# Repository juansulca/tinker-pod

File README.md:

# TinkerPod

Open-Source | DIY | Multitool | Modular | Extendable

The TinkerPod is an Open-Source hardware platform designed to appeal to makers, creative coders,
and designers by providing a hackable and customizable hardware. Inspired by the evolution of
multitools and influenced by contemporary devices like the Flipper Zero and SQRT,
this project explores the application of critical making, and personal fabrication to Open-Source hardware.
The TinkerPod is an ideal hardware platform for designers and makers to explore, learn, modify and extend; make it your own!

## Versions

The TinkerPod was designed to have 3 versions. All the versions are currently supported.
The main difference between versions is the parts list, complexity of assembly and features.

- [v1 TinkerArt](v1/): This version offers generative art functionality and can be programmed to create unique art pieces.
- [v2 TinkerPlay](v2/): This version offers a variety of games and functions, including games like pong, a timer, an etch-a-sketch inspired drawing function
  and a generative art function out of the box.
- [v3 TinkerPod](v3/): This version is an enhanced version of v2, running the same firmware but with additional features like a vibratioin sensor,
  hardware debouncing for the buttons and a fully integrated PCB.

## Hardware

This project was designed to work around the QT PY RP2040 from Adafruit. Despite this, it is possible to run the TinkerPod with
other microcontrollers with the same pinout and form factor from other manufacturers. This includes other boards from
Adafruit (QT PY line), the XIAO boards from Seeed Studio, among others.

TinkerPod v1, does not include a PCB and can be wired without tools using a tiny solderless breadboard, the display, microcontroller, and the case.

For ease of assembly starting from V2, the Screen for the TinkerPod is a 1.5" grayscale OLED display with the SSD1327 controller using a STEMMA cable. This display can be found from Adafruit and
other manufacturers but the Adafruit version is recommended due to the STEMMA cable, that reduces complexity for the assembly.

The TinkerPod v2 and v3 include PCB designs and schematics and require soldering.
A detailed assembly guide can be found along side the version files.

The hardware for this project took inspiration from the following sources:

- [Adafruit Charger BFF for QT Py](https://github.com/adafruit/Adafruit-Charger-BFF-PCB?tab=readme-ov-file#adafruit-charger-bff-for-qt-py-pcb)
- [Soldered Inkplate 2](https://github.com/SolderedElectronics/Soldered-Inkplate-2-hardware-design/tree/main)

## Firmware

All versions of the TinkerPod run on CircuitPython. The included firmware includes assets and base functionality.
You can modify the the firmware and add or change the functionality of the TinkerPod.

If you want to get started writing your own firmware and functionality, you can start with the [examples](examples/) directory.
This will provide the bassis for modifying the firmware and adding new functionality.

## Case

The case for the TinkerPod designed for 3D printing and can be printed using any FDM printer.
Printing settings are provided with each version files.

The cases for all versions were tested and printed using PLA and PETG. With the best results being
achieved with PETG on a textured plate.

Alternative cases can be found in the variants directory.

## Documentation

General guides can be found in the [docs](docs/) directory, including a simple guide to install CircuitPython and
managing the dependencies for the firmware.

## Acknowledgements

The hardware for this project took inspiration from the following sources:

- [Adafruit Charger BFF for QT Py](https://github.com/adafruit/Adafruit-Charger-BFF-PCB)
- [Soldered Inkplate 2](https://github.com/SolderedElectronics/Soldered-Inkplate-2-hardware-design/tree/main)
- [SQRT](https://ksawerykomputery.com/works/sqrt)
- [Button debounce article](https://hackaday.com/2015/12/09/embed-with-elliot-debounce-your-noisy-buttons-part-i/)

## Contributions

Contributions are welcome and appreciated. If you have any suggestions or improvements, please feel free to open an issue or submit a pull request.

## License

The TinkerPod is licensed under the following terms:

- Software: MIT License (see [LICENSE](LICENSE))
- Hardware: CERN Open Hardware Licence Version 2 - Permissive (see [LICENSE_OHL](LICENSE_OHL))
- Documentation: CC-BY-SA-4.0 (see [LICENSE_CC](LICENSE_CC))

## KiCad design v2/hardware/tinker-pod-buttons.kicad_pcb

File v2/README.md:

# TinkerPod v2

TinkerPod v2 is a more advanced version of the tinkerpod. This version includes 4 buttons and an optional LiIon charger and battery.
This version can be powered using a USB-C cable with a powerbank, phone or USB-C charger.
The firmware included with this version includes more applications and a application menu.

## Parts List

| Item                              | Quantity | Description                                          |
| --------------------------------- | -------- | ---------------------------------------------------- |
| Adafruit QT PY RP2040             | 1        | Can be replaced with XIAO pinout boards              |
| Adafruit 1.5" Gray scale OLED     | 1        | SSD1327 driver chip, SPI/I2C interface               |
| TinkerPod v2 PCB                  | 1        |                                                      |
| STEMMA QT/Qwiic cable             | 1        | 50mm long                                            |
| Push buttons                      | 4        | 8mm rubber dome push buttons                         |
| Adafruit LiIon Charger BFF Add-On | 1        | (Optional battery powered)                           |
| Lithium Ion Polymer Battery       | 1        | (Optional battery powered) 3.7v – 420mAh single cell |
| Threaded Inserts                  | 8        |                                                      |
| M2 machine screws                 | 8        | M2 size bolts (4mm x2, 6mm x6)                       |
| TinkerPod v2 3D printed case      | 1        |                                                      |

## Required tools:

| Item           | Description                             |
| -------------- | --------------------------------------- |
| Soldering Iron | Preferably one with a fine tip          |
| Solder         | Rosin core, preferably thin             |
| Flux           | Paste or pen                            |
| Hex key        | Or screw driver depending on the screws |
| Twezzers       | (optional)                              |
| USB-C cable    | USB C **data** cable (USB C to C/A)     |

## Assembly

1. Flash circuit python on the QT PY RP2040.
   1. Open the official [site](https://circuitpython.org/board/adafruit_qtpy_rp2040/) and download the latest version of CircuitPython.
   2. While holding the _boot_ button in the QT PY, plug it into a computer using the USB-C cable. Different version of the QT PY might need a different button to access bootloader mode, please check the official [docs](https://learn.adafruit.com/welcome-to-circuitpython/installing-circuitpython) for the specific board.
      
   3. The device should appears mounted in the OS as **RPI-RP2**, this might be different for other boards other than the RP2040 board.
   4. Drag and drop the `.UF2` file (downloaded in step 1) to the `RPI-RP2` boot drive.
   5. After a couple of seconds the onboard neopixel (LED) will flash and a new drive will appear in the computer, this time it should be called **CIRCUITPY**.
   6. ⚠️ Always eject the device before unplugging the cable.
2. (Optional) Solder the LiIon Charger BFF to the PCB.
   1. Place the PCB donut side down. The **TinkerPod** and **v2** silkscreen labels should be visible.
   2. Carefully line up the BFF with the PCB, in the M2 space, also marked as BFF LiPo charger. The JST connector (white box) should be facing the **v2** text on the PCB.
      
   3. Solder all the pads. take extra care on the 5V and GND pads.
      
3. Solder the QT PY to the PCB.
   1. Place the PCB donut side down. The **TinkerPod** and **v2** silkscreen labels should be visible.
   2. Carefully line up the QT PY with the PCB, in the `M1` space also marked on the side as `QT PY RP2040`. The pads can be identified for the cutout in the middle. Make sure the USB port is pointing towards the outside of the board and the reset and boot buttons and the STEMMA connector are accessible.
      
   3. Solder the **14** pins, 7 on each side.
      
4. Solder the 4 buttons to the PCB.
   1. After completing steps 2 and 3, flip the PCB (Donut side up).
      
   2. Place the buttons in the markers SW1, SW2, SW3, SW4.
      
   3. Flip the PCB again (Donut side down).
   4. Solder all 4 pins of every push button. (16 solder joins in total).
      
5. Now is a great moment to flash the firmware and test the TinkerPod before installing it into the case.
   1. Connect the STEMMA connector to the QT PY and Screen. It should slide in place without force.
      
   2. (Optional) Connect the battery using the JST connector in the BFF board.
      
   3. Download the TinkerPod firmware from GitHub. (firmware folder)
   4. Using a USB C data cable. Plug the device to the computer.
   5. Copy the content of the firmware folder (where the `code.py`file is) to the device.
   6. Remember to copy the `lib`directory.
   7. Alternatively check this project documentation for alternative installation methods.
   8. The splash screen followed by the menu should appear. Navigate the menu and use the applications by pressing the 4 buttons.
   9. The charging indicator (orange LED) in the BFF board should light up if there is a battery connected and the BFF installed.
      
   10. If everything works as expected, continue with the next step.
       1. If something is not working:
       2. Check for cold solder joins
       3. Verify that that the firmware was flashed correctly.
       4. If there is red LED flashing there is an issue with the firmware.
   11. Eject the device and unplug the USB cable.
6. Place the 3D printed buttons in the enclosure and make sure they slide smooth.
   
7. Prepare the bottom enclosure.
   1. Place the threaded inserts in the holes located in the top part of the enclosure.
      
   2. Using the soldering iron push the inserts as straight as possible until they are flush with the surface of the enclosure.
      
   3. Place the PCB in place (with the USB-C port towards the hole in the enclosure) and screw it in place using the M2 machine screws.
   4. Make sure the power switch on the BFF board is in the _off_ position.
   5. Plug in the battery.
      
   6. Secure the battery using the battery bracket and some double sided tape.
8. Prepare the screen assembly
   1. Place the threaded inserts in the holes located in the top part of the enclosure.
   2. Using the soldering iron push the inserts as straight as possible until they are flush with the surface of the case.
      
   3. Connect the STEMMA cable into the screen, it should slide in place without force.
   4. Gently place the 1.5" screen into the slot, do not apply pressure on the scree.
      
   5. Place the screen supports and line up the holes. The rectangular piece should go towards the top (can be placed in any orientation) and the remaining piece should go to the bottom. The bottom piece will only line up one way, with the legs pointing to the top.
   6. Screw the supports to the top case, tighten the screws until there is some resistance. Do not over tighten the screws.
      
   7. The screen might have some play, this is expected. And some gaps might be visible from the front side, which is also expected.
9. Closing the case.
   1. Plug the other side of the STEMMA connector to the QT PY.
      
   2. Using the power switch in the BFF board, turn the device _on_.
   3. Gently push the two parts of the case together.
10. Happy tinkering!

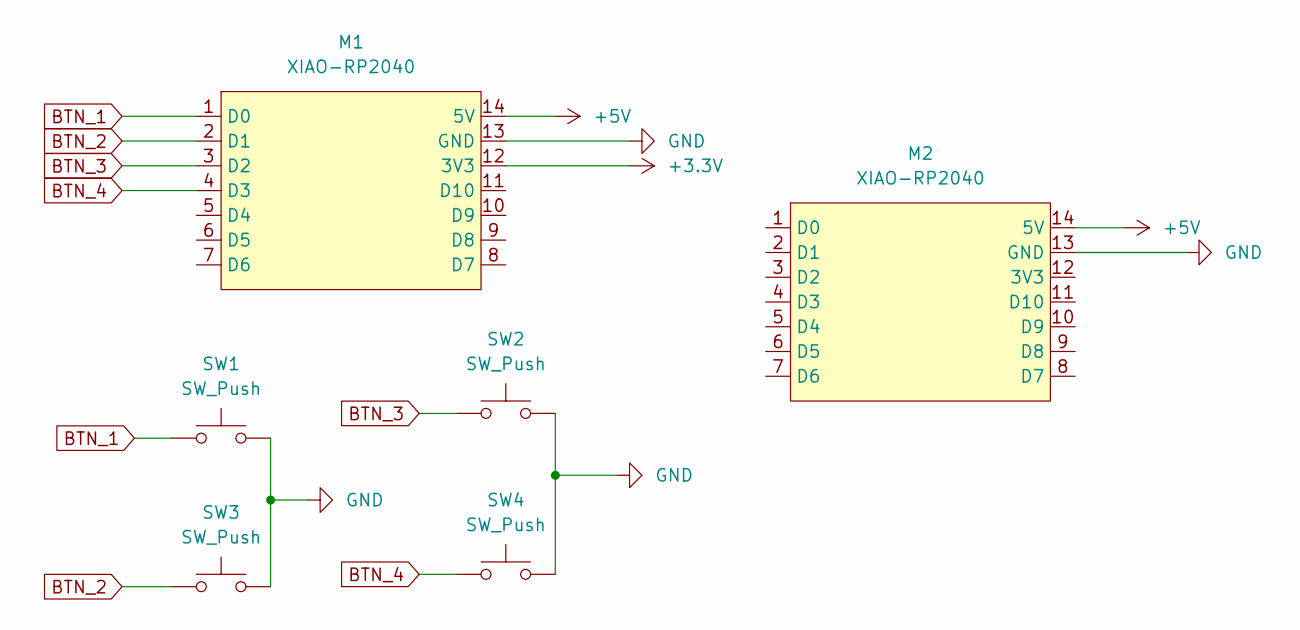
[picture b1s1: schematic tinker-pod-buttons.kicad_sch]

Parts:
M1: XIAO-RP2040; QTPYRP2040
M2: XIAO-RP2040; XIAO-SAMD21-RP2040-14P-2.54-21X17.8MM (Seeeduino XIAO)
SW1, SW2, SW3, SW4: SW_Push; 3101

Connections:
+3.3V: M1.12 (3V3)
+5V: M1.14 (5V), M2.14 (5V)
BTN_1: M1.1 (D0), SW1.1
BTN_2: M1.2 (D1), SW3.1
BTN_3: M1.3 (D2), SW2.1
BTN_4: M1.4 (D3), SW4.1
GND: M1.13 (GND), M2.13 (3V3), SW1.2, SW2.2, SW3.2, SW4.2

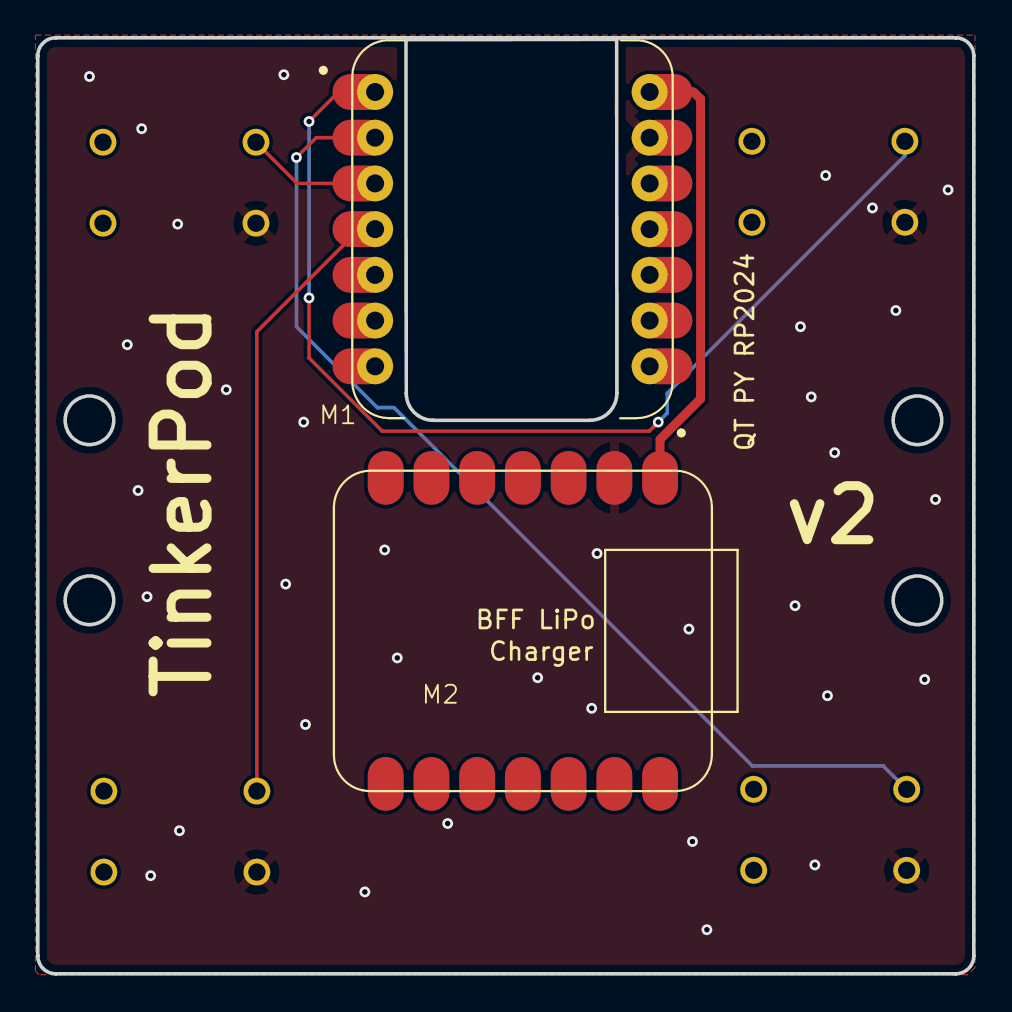
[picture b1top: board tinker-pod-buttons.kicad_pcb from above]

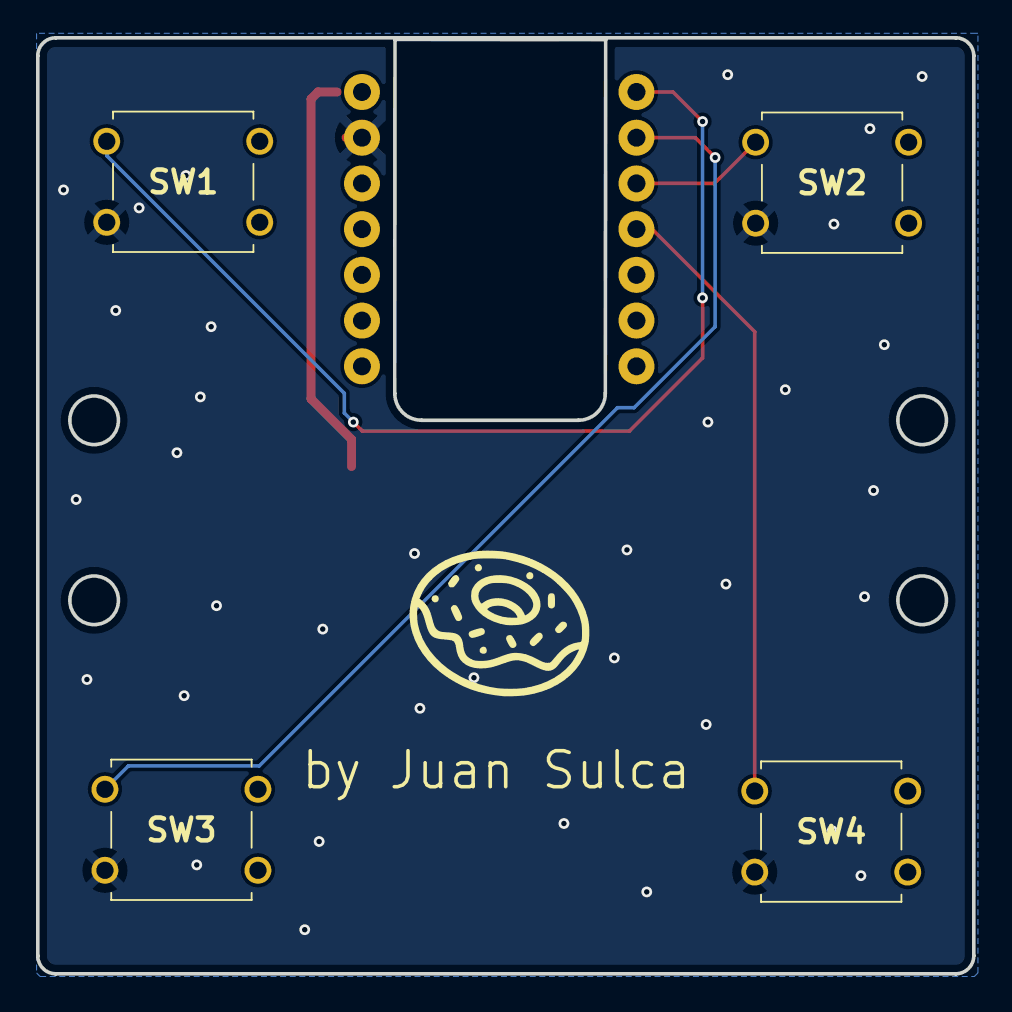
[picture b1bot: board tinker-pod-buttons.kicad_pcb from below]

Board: 2 copper layers, 52.0 x 52.0 mm, 6 parts (4 on the bottom side), 6 nets.

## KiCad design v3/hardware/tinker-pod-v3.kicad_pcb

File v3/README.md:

# TinkerPod v3 (latest)

The latest evolution of TinkerPod delivers enhanced functionality and streamlined design through single-PCB integration. This version builds upon its predecessors, offering improved features and more robust implementation while maintaining the platform's core functionality.

The CAD and productions files for v3 con be found in the [hardware](hardware/) directory. Which is devided in:

- PCB
  - Schematic
  - PCB Layout
  - Bill of Materials
  - Gerber Files
- Case
  - Case Design
  - 3D models

The assembly instruction can be found on this page.

## v3 PCB

### Bill Of Materials

| Qty | Value                        | Package        | Designator     | Part number                              |
| :-- | ---------------------------- | -------------- | -------------- | ---------------------------------------- |
| 4   | .1uF, ceramic, 25V, 10%, X5R | 1210           | C1, C2, C3, C4 | KEMET - C1210X104K1RACTU                 |
| 2   | 10uF, ceramic, 16V, 10%, X5R | 1210           | C5, C6         | KEMET - C1210C106K3RACAUTO               |
| 1   | LED                          | 1206           | D1             | Broadcom - HSMG-C150                     |
| 1   | Schottky Diodes, 1A, 20V     | SOD-123        | D2             | onsemi - MBR120ESFT1G                    |
| 1   | B2B-PH-SM4-TB                | B2BPHSM4TBLFSN | J1             | JST - B2BPHSM4TBLFSN                     |
| 4   | 1K, 1/4W, 1%                 | 1206           | R1, R2, R3, R4 | Vishay / Beyschlag - MCA12060C1001FP500  |
| 2   | 5.1K, 1/4W, 0.1%             | 1206           | R5, R6         | Panasonic - ERA-8ARB512V                 |
| 1   | MCP73831T-2ACI/OT            | SOT-23-5       | U2             | Microchip Technology - MCP73831T-2ACI/OT |
| 1   | DPDT                         | JS202011AQN    | S5             | C&K - JS202011AQN                        |

### Assembly

1. Secure the PCB with the TP v3 label facing up.
   
2. Apply paste in all the SMD pads, except for the QT PY pads, D1 and J1.
   1. Best results were achieved soldering the LED (D1) and JST (J1) connector with a soldering iron.
   2. Apply solder paste to the pads, but enough to cover the pad but not a blob bigger than the pad.
      
3. Use tweezers or a tiny plastic point to remove excess solder paster.
4. Place the components that do not have polarity.
   1. Place C1, C2, C3, C4 - the .1uF capacitors.
   2. Place R1, R2, R3, R4 - 1k resistors.
   3. Place C5, C6 - 10uF capacitors.
      
   4. Place R5, R6 - 5.1K resistors.
5. Place the components with polarity

   1. Place D2: diode with the line facing the closed side of the rectangle
   2. Place U2: the battery charging IC

      1. The side with 3 legs should match the side with the tiny arrow

6. Solder the components using a hot air reflow station.
   1. According to the specification of the solder paste, set the temperature, starts from the lowest recommended temperature.
   2. Start from far away with a medium to low airflow.
   3. Approach the individual components and make sure they fall correctly into place.
      
   4. After all components are soldered, visually inspect the joints, make sure the are no pads shorting and that all the paste melted. Be careful, the PCB might be hot
      
   5. If there are shorting pads, retouch them with a soldering iron and some flux.
7. Solder D1 LED
   1. Check the polarity of the LED
   2. Place the LED with the Cathode (-) towards the closed side of the rectangle
   3. With the help of tweezers , solder the LED in place with a soldering iron.
      
8. Solder J1 JST connector.
   1. Apply some flux on the pads.
   2. Place the JST connector in place, aligning the box with the body of the connector.
   3. With the soldering iron carefully solder one of the legs of the connector.
   4. Solder the remaining legs, not much solder is needed.
      
9. Solder the S5 slide switch.
   1. Place the switch from the side. (TP v3 side)
      
   2. Flip The PCB (Tinkerpod pixelated logo up)
   3. Solder the six pins.
      
10. The PCB assembly will continue in the next section.

## Parts List

| Item                          | Quantity | Description                             |
| ----------------------------- | -------- | --------------------------------------- |
| Adafruit QT PY RP2040         | 1        | Can be replaced with XIAO pinout boards |
| Adafruit 1.5" Gray scale OLED | 1        | SSD1327 driver chip, SPI/I2C interface  |
| TinkerPod v3 PCB              | 1        |                                         |
| STEMMA QT/Qwiic cable         | 1        | 50mm long                               |
| Push buttons                  | 4        | 8mm rubber dome push buttons            |
| Threaded Inserts              | 8        |                                         |
| M2 machine screws             | 8        | M2 size bolts (4mm x2, 6mm x6)          |
| TinkerPod v2 3D printed case  | 1        |                                         |

## Assembly

1. Flash circuit python on the QT PY RP2040.
   1. Open the official [site](https://circuitpython.org/board/adafruit_qtpy_rp2040/) and download the latest version of circuit python.
   2. While holding the _boot_ button in the QT PY, plug it into a computer using the USB-C cable. Different version of the QT PY might need a different button to access bootloader mode, please check the official [docs](https://learn.adafruit.com/welcome-to-circuitpython/installing-circuitpython) for the specific board.
      
   3. The device should appears mounted in the OS as **RPI-RP2**, this might be different for other boards other than the RP2040 board.
   4. Drag and drop the `.UF2` file (downloaded in step 1) to the `RPI-RP2` boot drive.
   5. After a couple of seconds the onboard neopixel (LED) will flash and a new drive will appear in the computer, this time it should be called **CIRCUITPY**.
   6. ⚠️ Always eject the device before unplugging the cable.
2. Solder the QT PY to the PCB.
   1. Place the PCB with the pixelated Tinkerpod logo facing down. The **TP v3** should be visible.
      
   2. Carefully line up the QT PY with the PCB, in the `QT PY RP2040` space. The pads can be identified for the cutout in the middle. Make sure the USB port is pointing towards the outside of the board and the reset and boot buttons and the STEMMA connector are accessible.
   3. Solder the **14** pins, 7 on each side.
      
3. Solder the 4 buttons to the PCB.
   1. Flip the PCB (pixelated TinkerPod logo facing up).
   2. Place the buttons in the markers SW1, SW2, SW3, SW4.
      
   3. Flip the PCB again (pixelated Tinkerpod logo facing down).
   4. Solder all 4 pins of every push button. (16 solder joins in total).
      
4. Solder the vibration sensor
   1. Bend the vibration sensor legs to 90 degrees.
   2. Put the vibration sensor into the SW1 slot. The vibration sensor does not have polarity.
      
   3. If needed use some tape to secure the vibration sensor in place while soldering.
   4. Flip the PCB (Tinkerpod logo up)
   5. Solder the two pins.
      
   6. If the pins seem a bit long, cut them with a pair of flush cutters.
      
5. Now is a great moment to flash firmware and test the TinkerPod before installing it into the case.
   1. Connect the STEMMA connector to the QT PY and Screen. It should slide in place without force.
   2. (Optional) Connect the battery using the JST connector in the BFF board.
   3. Download any of the TinkerPod examples from GitHub. (examples folder)
   4. Using a USB C data cable. Plug the device to the computer.
   5. Copy the content of the firmware folder (where the `code.py`file is) to the device.
   6. Do not forget to copy the `lib`directory.
   7. Alternatively install the dependencies for the firmware using `circup`.
   8. The splash screen followed by the menu should appear. Navigate the menu and use the applications by pressing the 4 buttons.
   9. A green LED should be _on_ if there is battery connected to the JST terminal.
   10. If everything works as expected, continue with the next step. If something is not working, check for cold solder joins and check that that the firmware was flashed correctly. If there is red LED flashing there is an issue with the firmware.
   11. Eject the device and unplug the USB cable.
6. Prepare the bottom case.
   1. Slide the battery bracket on the PCB.
   2. Place the PCB in place (with the USB-C port towards the hole in the enclosure) and screw it in place using the M2 machine screws.
      
   3. Push the 3D printed on/off switch and make sure the power switch is in the _off_ position (right side).
      
7. Prepare the screen assembly
   1. Connect the STEMMA cable into the screen, it should slide in place without force.
   2. Gently place the 1.5" screen into the slot, do not apply pressure on the screen.
   3. Place the screen supports and line up the holes. The rectangular piece should go towards the top (can be placed in any orientation) and the remaining piece should go to the bottom. The bottom piece will only line up one way, with the legs pointing to the top.
      
   4. Screw the supports to the top enclosure, tighten the screws until there is some resistance. Do not over tighten the screws.
   5. The screen might have some play, this is expected. And some gaps might be visible from the front side, which is also expected.
8. Closing the enclosure.
   1. Plug the other side of the STEMMA connector to the QT PY.
      
   2. Plug in the battery.
      
   3. Secure the battery using the battery bracket and some double-sided tape.
      
   4. Close the enclosure
9. Turn on your device
10. Happy Tinkering!

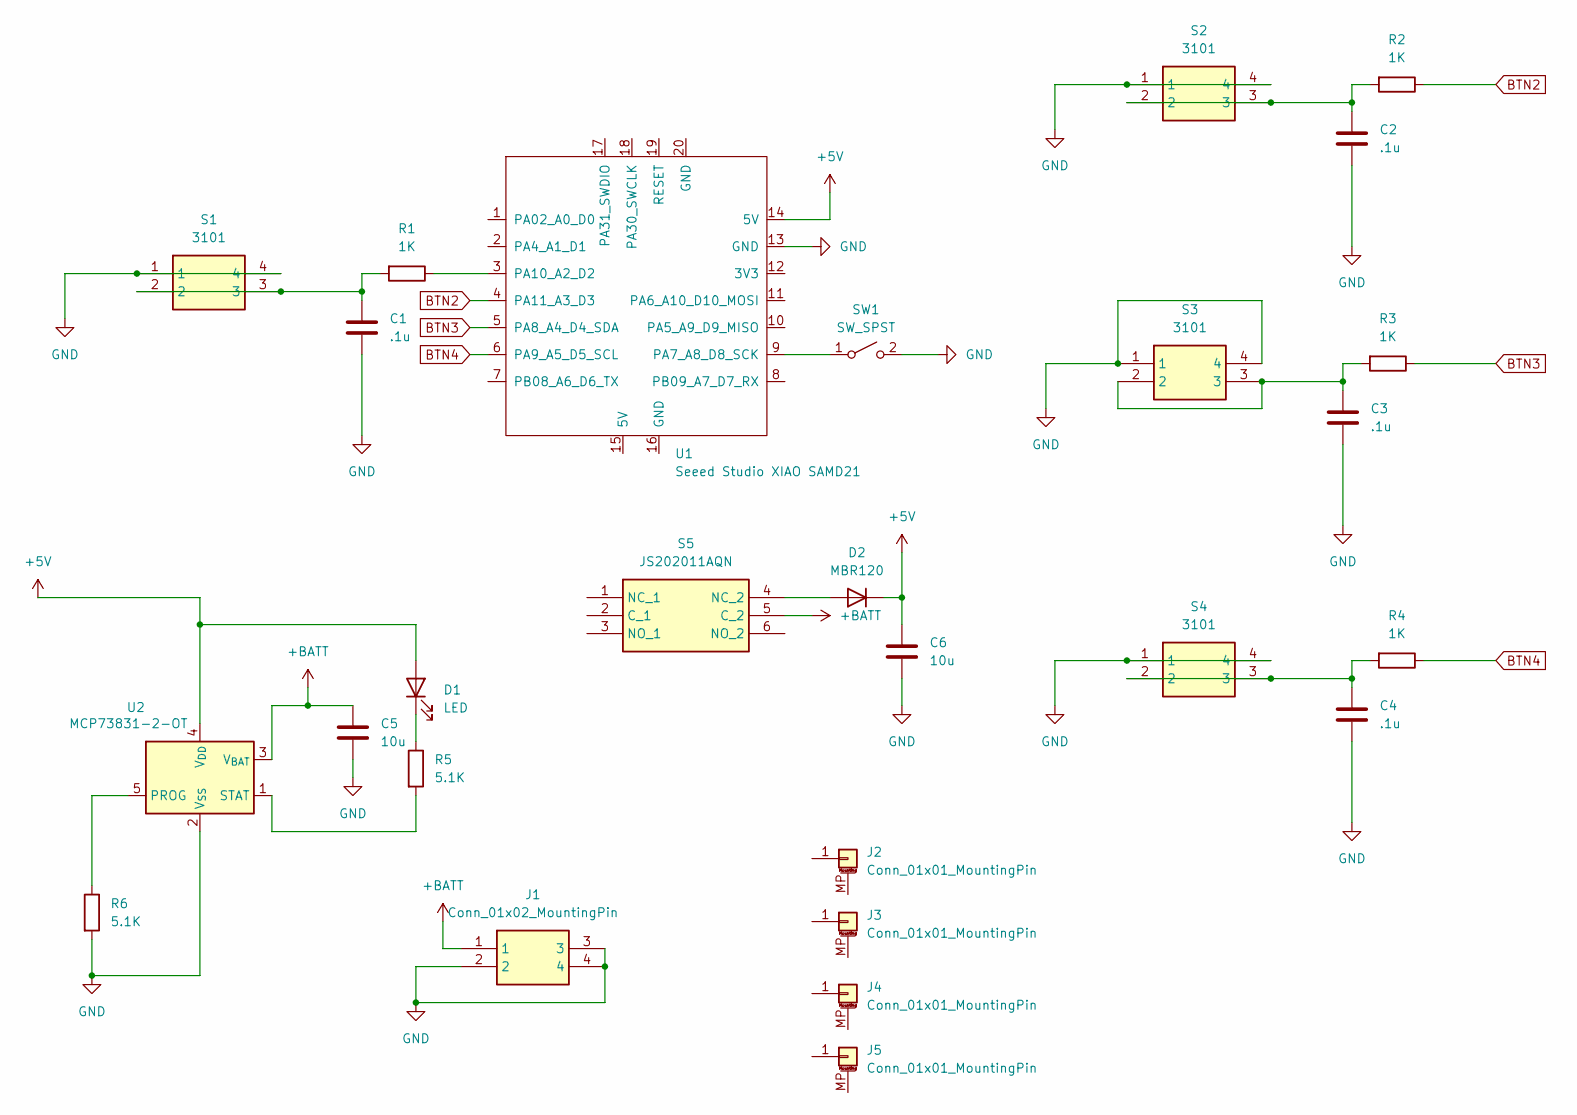
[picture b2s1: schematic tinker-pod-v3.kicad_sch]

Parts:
C1, C2, C3, C4: .1u; C_1210_3225Metric_Pad1.33x2.70mm_HandSolder
C5, C6: 10u; C_1210_3225Metric_Pad1.33x2.70mm_HandSolder
D1: LED; LED_1206_3216Metric_Pad1.42x1.75mm_HandSolder
D2: MBR120; D_SOD-123
J1: Conn_01x02_MountingPin; B2BPHSM4TBLFSN; Mouser Part Number N/A
J2, J3, J4, J5: Conn_01x01_MountingPin; MountingHole_2.2mm_M2
R1, R2, R3, R4: 1K; R_1206_3216Metric_Pad1.30x1.75mm_HandSolder
R5, R6: 5.1K; R_1206_3216Metric_Pad1.30x1.75mm_HandSolder
S1, S2, S3, S4: 3101; Mouser Part Number 485-3101
S5: JS202011AQN; Mouser Part Number 611-JS202011AQN
SW1: SW_SPST; CP_Radial_D4.0mm_P1.50mm
U1: Seeed Studio XIAO SAMD21; XIAO-SAMD21-RP2040-14P-2.54-21X17.8MM (Seeeduino XIAO)
U2: MCP73831-2-OT; SOT-23-5

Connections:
+5V: C6.1, D1.2 (A), D2.1 (K), U1.14 (5V), U2.4 (V_{DD})
+BATT: C5.1, J1.1, S5.5 (C_2), U2.3 (V_{BAT})
BTN2: R2.1, U1.4 (PA11_A3_D3)
BTN3: R3.1, U1.5 (PA8_A4_D4_SDA)
BTN4: R4.1, U1.6 (PA9_A5_D5_SCL)
GND: C1.2, C2.2, C3.2, C4.2, C5.2, C6.2, J1.2, J1.3, J1.4, R6.2, S1.1, S1.4, S2.1, S2.4, S3.1, S3.4, S4.1, S4.4, SW1.2 (B), U1.13 (GND), U2.2 (V_{SS})
unnamed: C1.1, R1.2, S1.2, S1.3
unnamed: C2.1, R2.2, S2.2, S2.3
unnamed: C3.1, R3.2, S3.2, S3.3
unnamed: C4.1, R4.2, S4.2, S4.3
unnamed: D1.1 (K), R5.1
unnamed: D2.2 (A), S5.4 (NC_2)
unnamed: SW1.1 (A), U1.9 (PA7_A8_D8_SCK)
unnamed: R1.1, U1.3 (PA10_A2_D2)
unnamed: R6.1, U2.5 (PROG)
unnamed: R5.2, U2.1 (STAT)

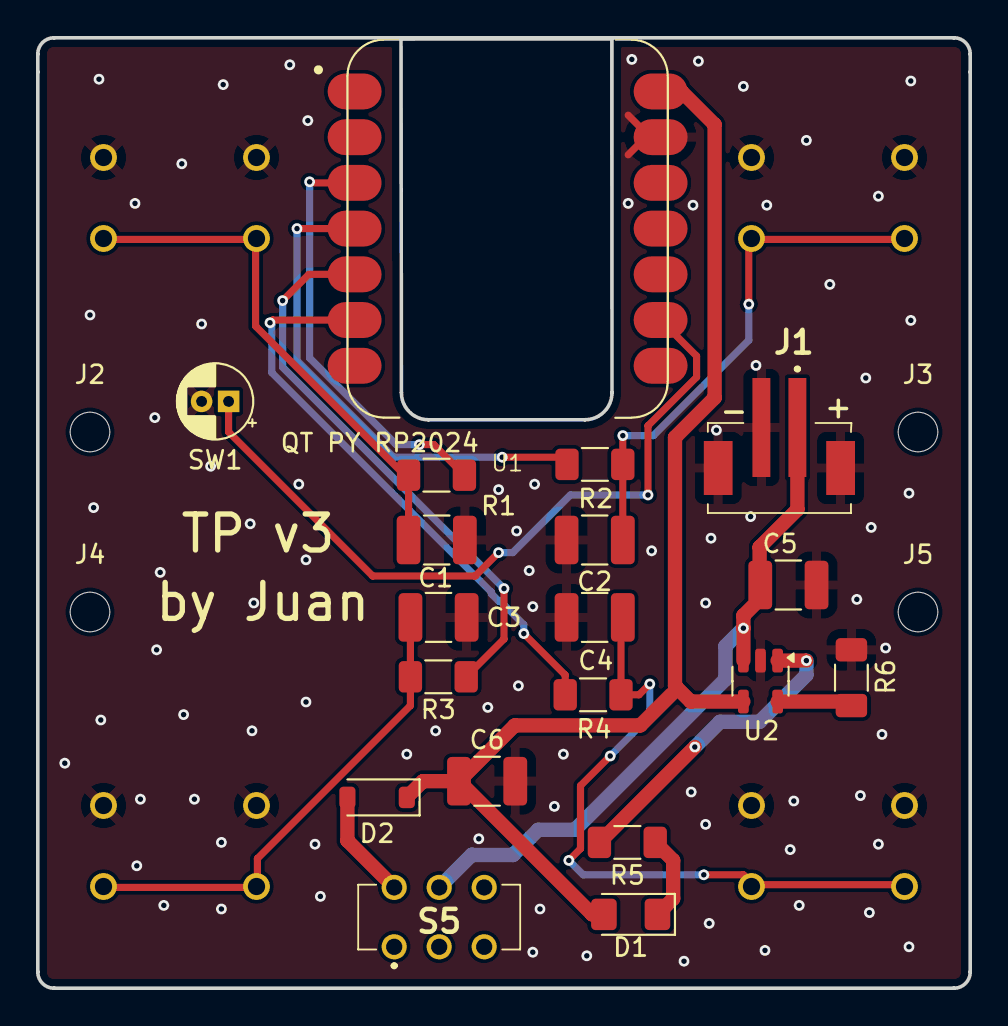
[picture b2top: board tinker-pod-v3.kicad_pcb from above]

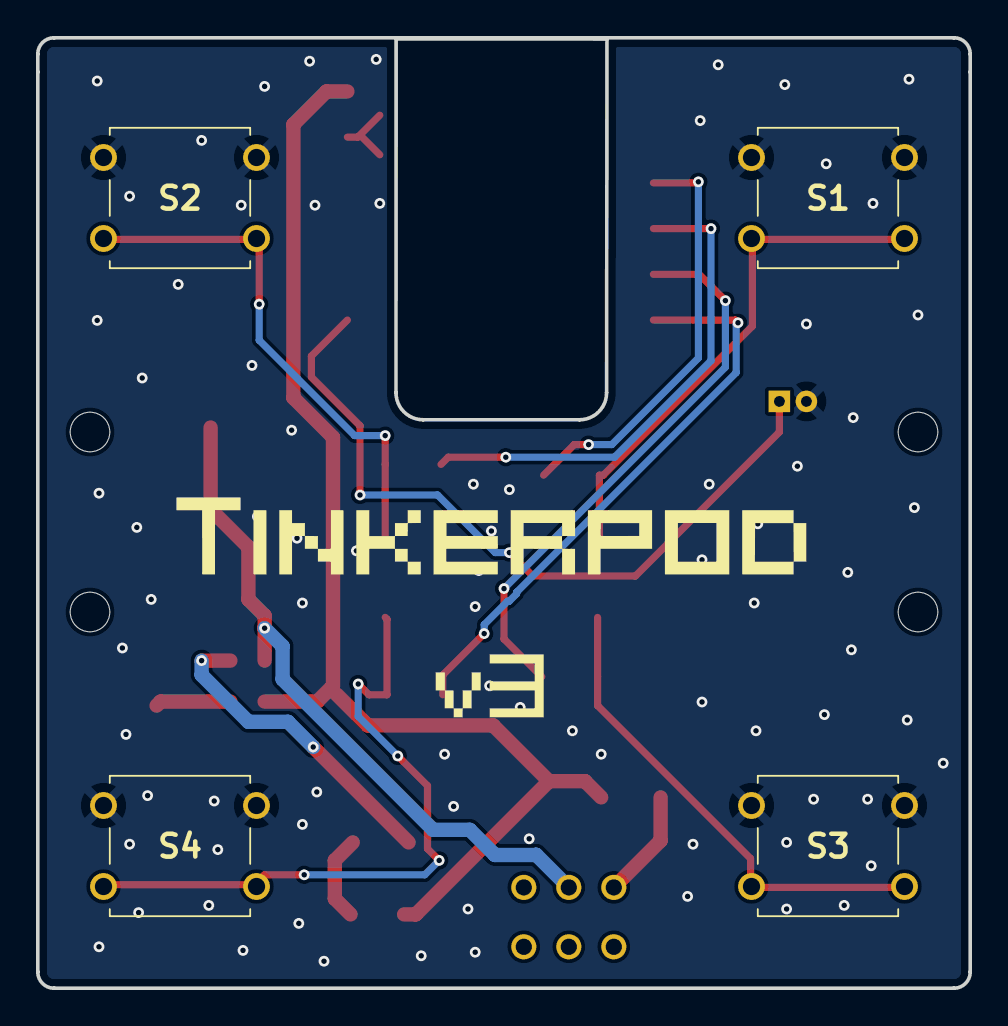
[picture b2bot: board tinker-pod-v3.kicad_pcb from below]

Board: 2 copper layers, 51.8 x 52.8 mm, 27 parts (4 on the bottom side), 16 nets.

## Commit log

2024-08-01 feat: Added v0.99 firmware
2024-08-08 Added lib folder in firmware
2024-08-08 Added .gitignore
2024-08-08 Added Readme
2024-08-08 Added case STL files
2024-09-19 Updated README with images
2024-09-19 Updated stl case designs to center usb port
2024-10-05 Updated TinkerArt code
2024-10-20 Initial pong implementation
2025-03-08 Pongo v1
2025-03-09 updated project structure
2025-03-09 added docs folder
2025-03-09 Added lib folder to examples
2025-03-09 Updated example readme files
2025-03-09 Updated v1 wiring diagram
2025-03-10 Added v1 mods
2025-03-10 Updated v1 firmware with comments
2025-03-10 fixed v1 Readme diagram
2025-03-10 Fixed code examples
2025-03-10 Added v2 assembly guide
2025-03-13 Added v2 firmware
2025-03-13 Added hardware projects to v2 and v3
2025-03-13 Added family photo to main readme
2025-03-13 Updated v1 assembly guide
2025-03-16 Updated license information
2025-03-16 Updated docs
2025-03-17 Added Firmware v3
2025-03-27 Uploaded CAD files for V1 and V3
2025-03-27 Added case files v2
2025-03-27 Updated family photo
2025-03-27 fixed v3 readme
2025-04-08 Updated doc images for v1
2025-04-08 Added v2 docs images
2025-04-09 Updated v3 assebly guide and images
2025-09-20 Updated v3 firmware
